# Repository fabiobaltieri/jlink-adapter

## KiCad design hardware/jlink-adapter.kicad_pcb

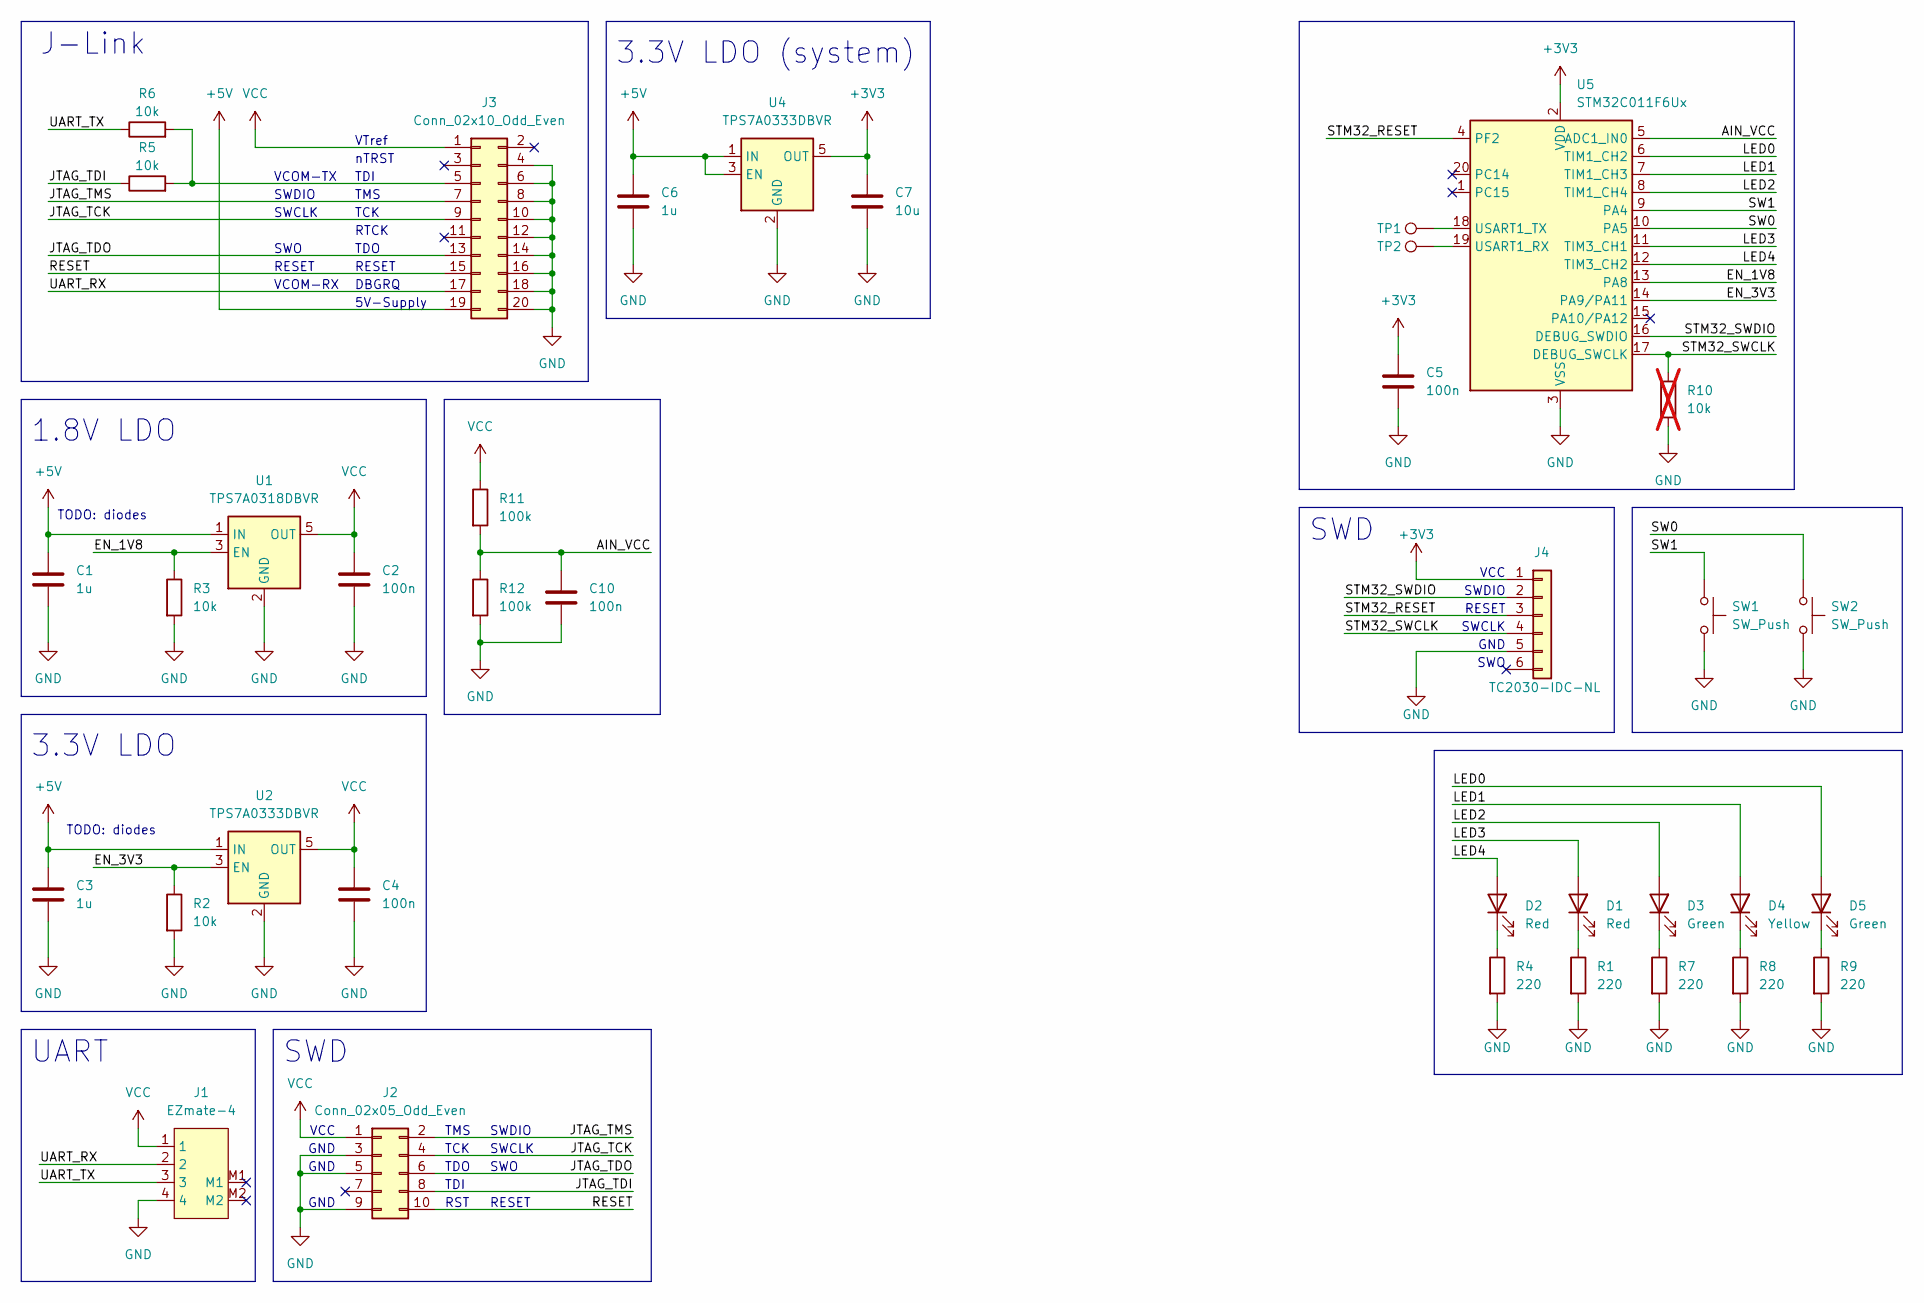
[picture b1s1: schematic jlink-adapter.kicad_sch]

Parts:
C1, C3, C6: 1u; C_0402_Worthington
C2, C4: 100n; C_0603_1608Metric
C5, C10: 100n; C_0402_Worthington
C7: 10u; C_0603_1608Metric
D1, D2: Red; LED_AA3528
D3, D5: Green; LED_AA3528
D4: Yellow; LED_AA3528
J1: EZmate-4
J2: Conn_02x05_Odd_Even; PinHeader_2x05_P1.27mm_Vertical_SMD
J3: Conn_02x10_Odd_Even; PinSocket_2x10_P2.54mm_Vertical_SMD
J4: TC2030-IDC-NL; Tag-Connect_TC2030-IDC-NL_2x03_P1.27mm_Vertical
R1, R4, R7, R8, R9: 220; R_0402_Worthington
R2, R3, R5, R6: 10k; R_0402_Worthington
R10: 10k; R_0402_Worthington; not fitted
R11, R12: 100k; R_0402_Worthington
SW1, SW2: SW_Push; SW_Push_1P1T_NO_Vertical_Wuerth_434133025816
TP1, TP2: TestPoint; TestPoint_Pad_D1.0mm
U1: TPS7A0318DBVR; SOT-23-5
U2, U4: TPS7A0333DBVR; SOT-23-5
U5: STM32C011F6Ux; ST_UFQFPN-20_3x3mm_P0.5mm

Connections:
+3V3: C5.1, C7.1, J4.1, U4.5 (OUT), U5.2 (VDD)
+5V: C1.1, C3.1, C6.1, J3.19, U1.1 (IN), U2.1 (IN), U4.1 (IN), U4.3 (EN)
/AIN_VCC: C10.1, R11.2, R12.1, U5.5 (ADC1_IN0)
/EN_1V8: R3.1, U1.3 (EN), U5.13 (PA8)
/EN_3V3: R2.1, U2.3 (EN), U5.14 (PA9/PA11)
/JTAG_TCK: J2.4, J3.9
/JTAG_TDI: J2.8, R5.1
/JTAG_TDO: J2.6, J3.13
/JTAG_TMS: J2.2, J3.7
/LED0: D5.2 (A), U5.6 (TIM1_CH2)
/LED1: D4.2 (A), U5.7 (TIM1_CH3)
/LED2: D3.2 (A), U5.8 (TIM1_CH4)
/LED3: D1.2 (A), U5.11 (TIM3_CH1)
/LED4: D2.2 (A), U5.12 (TIM3_CH2)
/RESET: J2.10, J3.15
/STM32_RESET: J4.3, U5.4 (PF2)
/STM32_SWCLK: J4.4, R10.1, U5.17 (DEBUG_SWCLK)
/STM32_SWDIO: J4.2, U5.16 (DEBUG_SWDIO)
/SW0: SW2.1, U5.10 (PA5)
/SW1: SW1.1, U5.9 (PA4)
/UART_RX: J1.2, J3.17
/UART_TX: J1.3, R6.1
GND: C1.2, C2.2, C3.2, C4.2, C5.2, C6.2, C7.2, C10.2, J1.4, J2.3, J2.5, J2.9, J3.4, J3.6, J3.8, J3.10, J3.12, J3.14, J3.16, J3.18, J3.20, J4.5, R1.2, R2.2, R3.2, R4.2, R7.2, R8.2, R9.2, R10.2, R12.2, SW1.2, SW2.2, U1.2 (GND), U2.2 (GND), U4.2 (GND), U5.3 (VSS)
unnamed: D1.1 (K), R1.1
unnamed: D2.1 (K), R4.1
unnamed: D3.1 (K), R7.1
unnamed: D4.1 (K), R8.1
unnamed: D5.1 (K), R9.1
unnamed: J3.5, R5.2, R6.2
unnamed: TP1.1, U5.18 (USART1_TX)
unnamed: TP2.1, U5.19 (USART1_RX)
VCC: C2.1, C4.1, J1.1, J2.1, J3.1, R11.1, U1.5 (OUT), U2.5 (OUT)

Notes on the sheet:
SWDIO
TDO
VCC
RESET
VCOM-RX
GND
SWD
SWO
TCK
RTCK
5V-Supply
RST
SWCLK
DBGRQ
TDI
UART
J-Link
TMS
nTRST
VTref
3.3V LDO
TODO: diodes
3.3V LDO (system)
VCOM-TX
1.8V LDO

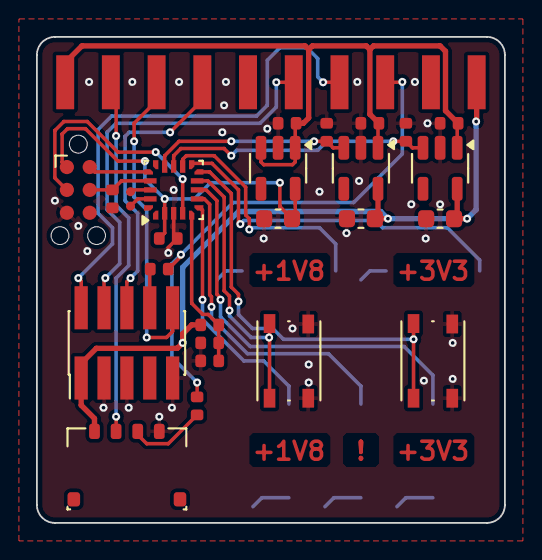
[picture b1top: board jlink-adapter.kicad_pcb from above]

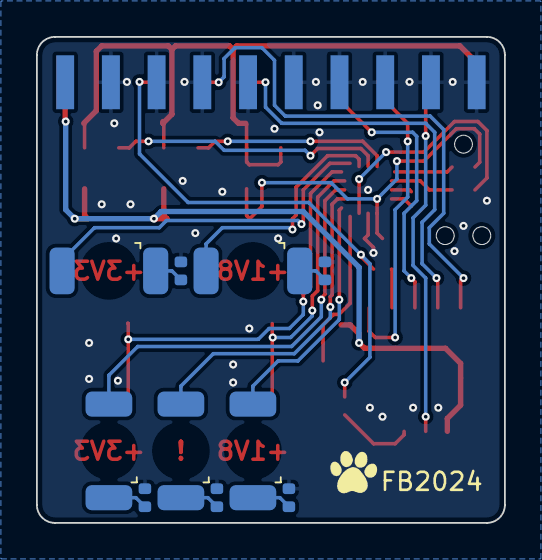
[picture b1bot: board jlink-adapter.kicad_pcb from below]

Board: 2 copper layers, 26.0 x 27.0 mm, 37 parts (10 on the bottom side), 32 nets.

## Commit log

2024-07-21 hw: fix led r values
2024-07-21 schematic cleanup
2024-07-30 fw: initial firmware
2024-07-30 hw: use lower output caps
2024-08-11 fw: use the upstream thread analyzer
2024-08-11 hw: update the step file name
2024-08-17 hw: add note about reverse diodes
2024-08-24 fw: drop trailing blank line
2024-11-17 fw: use led_dt_spec
2024-12-05 hw: assembly fixes
2024-12-05 fw: adjust low threshold to 150mV
2024-12-30 fw: st adc api update
2025-01-31 hw: add pdf schematics
